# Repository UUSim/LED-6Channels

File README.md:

# 6 Channel LED controller board
This project hosts the Eagle-based design of a 6 channel LED controller.

The device features:
- DC power (rated 7-12V)
- Powered via i2c bus connector (TBD)
- Controlled via 3 rotary encoders:
  - Intensity for 2 separate LED sections
  - One color wheel
- Clock with battery backup
- Programming header
- External i2c-bus connector

The 6 channels are configured as follows:
- 1 RGB connector
- 3 separate connectors for a color of choice

Note: The board is layed out such that diy etching is possible using double-sided UV-lighting and etching. The traces are routed such that the number of vias is kept to a minimum (avoiding trough-hole plating).

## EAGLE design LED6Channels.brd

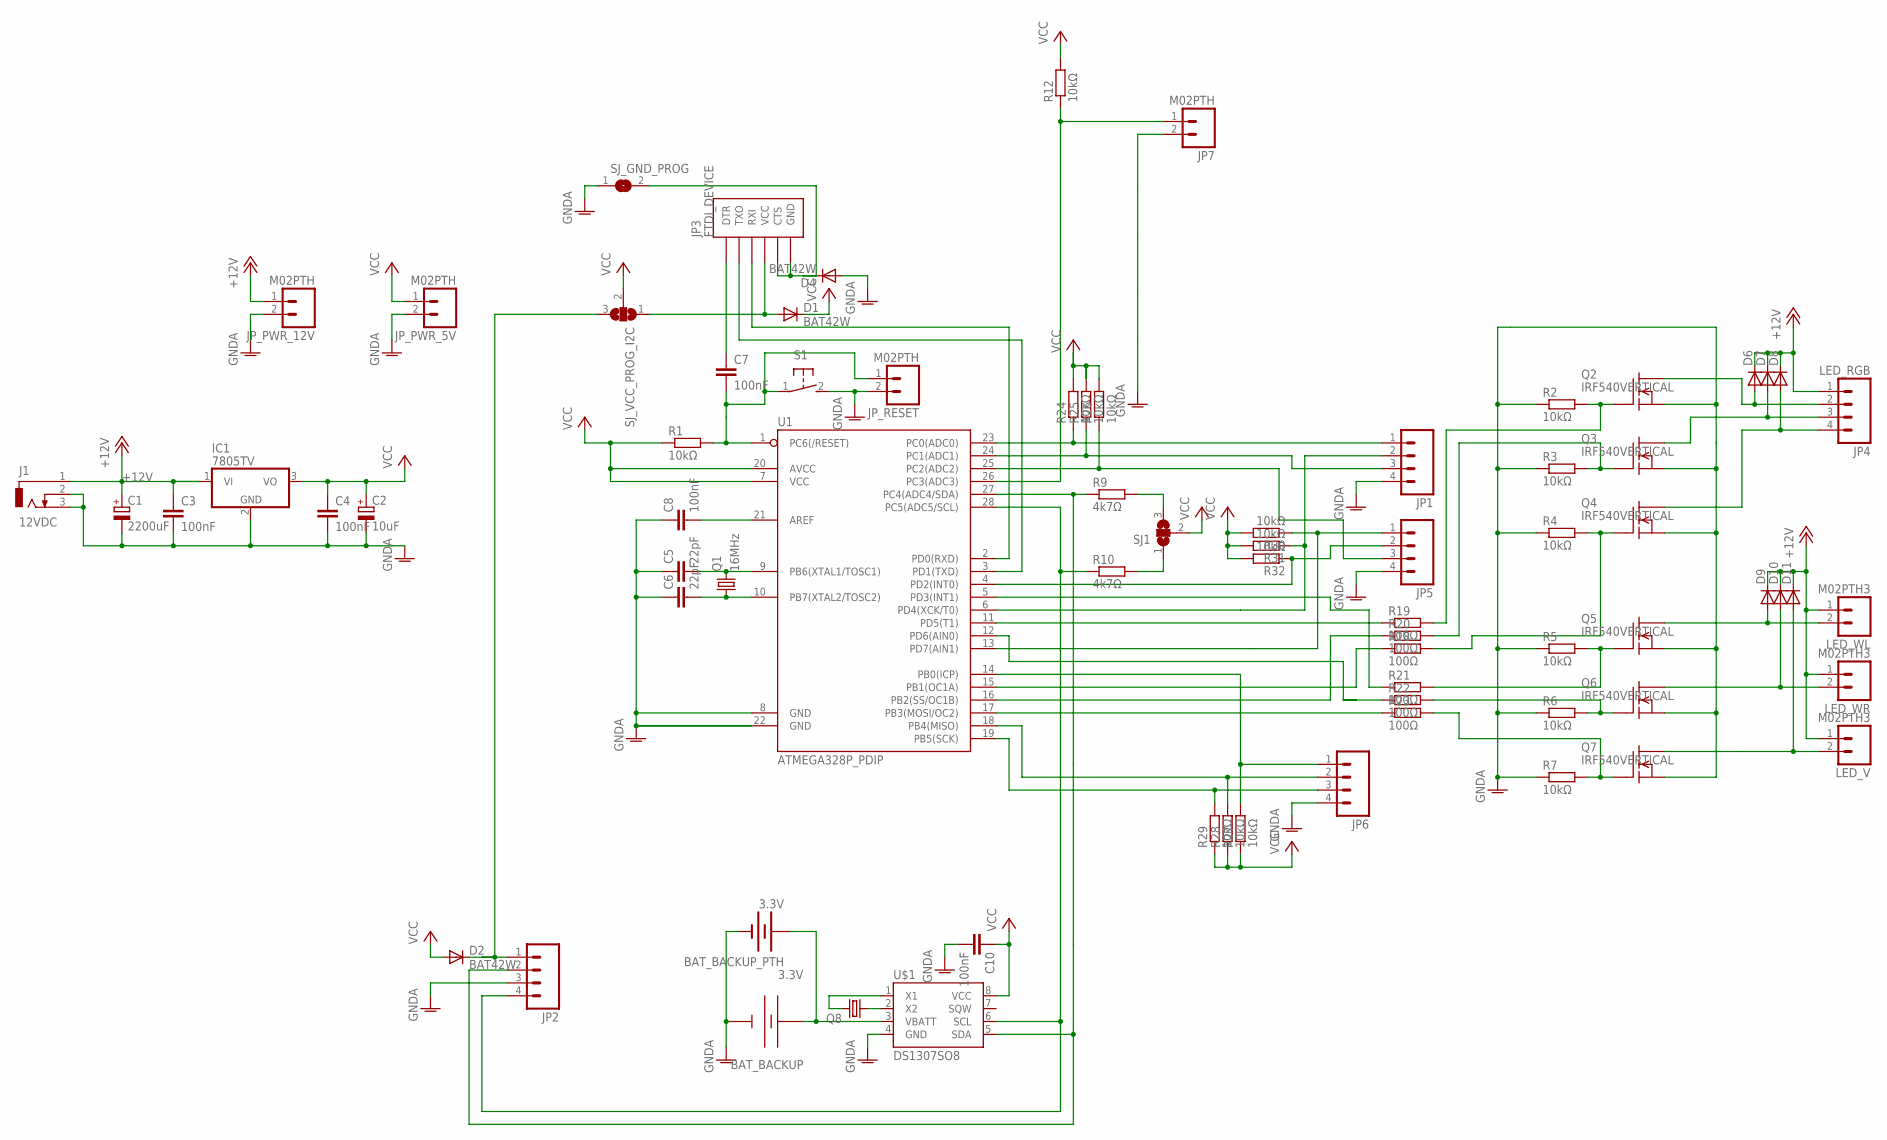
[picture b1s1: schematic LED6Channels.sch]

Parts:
BAT_BACKUP: 3.3V; S8421-45R-NOVIAS
BAT_BACKUP_PTH: 3.3V; BATTCOM_20MM_PTH
C1: 2200uF; E5-13
C2: 10uF; E2-5
C3, C4, C7, C8, C10: 100nF; C025-024X044
C5, C6: 22pF; C025-024X044
D1, D2, D4: BAT42W; SOD123
D6, D7, D8, D9, D10, D11: DIODE-DO201-05V; DO201AD-05V
IC1: 7805TV; TO220V
J1: 12VDC; DCJ0303
JP1, JP2, JP5, JP6: M04LONGPADS; 1X04_LONGPADS
JP3: FTDI_DEVICE; FTDI_DEVICE_SIDE
JP4: LED_RGB; 1X04_LONGPADS
JP7: M02PTH; 1X02
JP_PWR_5V, JP_PWR_12V: M02PTH; 1X02
JP_RESET: M02PTH; 1X02
LED_V: M02PTH3; 1X02_LONGPADS
LED_WL: M02PTH3; 1X02_LONGPADS
LED_WR: M02PTH3; 1X02_LONGPADS
Q1: 16MHz; HC49/S
Q2, Q3, Q4, Q5, Q6, Q7: IRF540VERTICAL; TO220V
Q8: CRYSTALTC26H; TC26H
R1, R2, R3, R4, R5, R6, R7, R12, R24, R25, R26, R27, R28, R29, R30, R31, R32: 10kΩ; 0207/10
R9, R10: 4k7Ω; 0207/10
R18, R19, R20, R21, R22, R23: 100Ω; 0207/10
S1: 31-XX; B3F-31XX
SJ1: SJ2W; SJ_2
SJ_GND_PROG: SJ
SJ_VCC_PROG_I2C: SJ2W; SJ_2
U1: ATMEGA328P_PDIP; DIL28-3
U$1: DS1307SO8; SO08

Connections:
+12V: C1.+, C3.1, D6.C, D7.C, D8.C, D9.C, D10.C, D11.C, IC1.1 (VI), J1.1, JP4.1, JP_PWR_12V.1, LED_V.1, LED_WL.1, LED_WR.1
E1_BUTTON: JP1.3, R25.1, U1.24 (PC1(ADC1))
E1_L: JP1.1, R24.1, U1.23 (PC0(ADC0))
E1_R: JP5.3, R26.1, U1.25 (PC2(ADC2))
E2_BUTTON: JP1.2, R31.1, U1.6 (PD4(XCK/T0))
E2_L: JP5.2, R32.1, U1.4 (PD2(INT0))
E2_R: JP5.1, R30.1, U1.13 (PD7(AIN1))
GNDA: BAT_BACKUP.2 (-), BAT_BACKUP_PTH.2 (-), C1.-, C2.-, C3.2, C4.2, C5.1, C6.1, C8.1, C10.2, D4.A, IC1.2 (GND), J1.2, J1.3, JP1.4, JP2.3, JP5.4, JP6.4, JP7.2, JP_PWR_5V.2, JP_PWR_12V.2, JP_RESET.2, Q2.3 (S), Q3.3 (S), Q4.3 (S), Q5.3 (S), Q6.3 (S), Q7.3 (S), R2.1, R3.1, R4.1, R5.1, R6.1, R7.1, S1.2 (S), SJ_GND_PROG.1, U1.8 (GND), U1.22 (GND), U$1.4 (GND)
unnamed: Q7.1 (G), R7.2, R23.2
unnamed: R23.1, U1.17 (PB3(MOSI/OC2))
unnamed: Q6.1 (G), R6.2, R22.2
unnamed: R20.1, U1.16 (PB2(SS/OC1B))
unnamed: R18.1, U1.15 (PB1(OC1A))
unnamed: R21.1, U1.5 (PD3(INT1))
unnamed: Q3.1 (G), R3.2, R20.2
unnamed: Q2.1 (G), R2.2, R19.2
unnamed: D10.A, LED_WR.2, Q6.2 (D)
unnamed: D9.A, LED_WL.2, Q5.2 (D)
unnamed: D11.A, LED_V.2, Q7.2 (D)
unnamed: D6.A, JP4.2, Q2.2 (D)
unnamed: D7.A, JP4.3, Q3.2 (D)
unnamed: C8.2, U1.21 (AREF)
unnamed: JP6.2, R28.2, U1.18 (PB4(MISO))
unnamed: JP6.3, R29.2, U1.19 (PB5(SCK))
unnamed: JP6.1, R27.2, U1.14 (PB0(ICP))
unnamed: Q5.1 (G), R5.2, R21.2
unnamed: R19.1, U1.11 (PD5(T1))
unnamed: R22.1, U1.12 (PD6(AIN0))
unnamed: Q4.1 (G), R4.2, R18.2
unnamed: D8.A, JP4.4, Q4.2 (D)
OSC1: C5.2, Q1.2, U1.9 (PB6(XTAL1/TOSC1))
OSC2: C6.2, Q1.1, U1.10 (PB7(XTAL2/TOSC2))
PIN_EXTRA: JP7.1, R12.1, U1.26 (PC3(ADC3))
P_GND: D4.C, JP3.P$5 (CTS), JP3.P$6 (GND), SJ_GND_PROG.2
P_RESET: C7.1, JP3.P$1 (DTR)
P_RX: JP3.P$3 (RXI), U1.2 (PD0(RXD))
P_TX: JP3.P$2 (TXO), U1.3 (PD1(TXD))
P_VCC: D1.A, JP3.P$4 (VCC), SJ_VCC_PROG_I2C.1
RESET: C7.2, JP_RESET.1, R1.2, S1.1, U1.1 (PC6(/RESET))
SCL: JP2.4, R10.1, U1.28 (PC5(ADC5/SCL)), U$1.6 (SCL)
SCL_PULLUP_JUMP: R10.2, SJ1.1
SDA: JP2.2, R9.1, U1.27 (PC4(ADC4/SDA)), U$1.5 (SDA)
SDA_PULLUP_JUMP: R9.2, SJ1.3
VBAT: BAT_BACKUP.1 (+), BAT_BACKUP_PTH.1 (+), U$1.3 (VBATT)
VCC: C2.+, C4.1, C10.1, D1.C, D2.A, IC1.3 (VO), JP_PWR_5V.1, R1.1, R12.2, R24.2, R25.2, R26.2, R27.1, R28.1, R29.1, R30.2, R31.2, R32.2, SJ1.2, SJ_VCC_PROG_I2C.2, U1.7 (VCC), U1.20 (AVCC), U$1.8 (VCC)
VCC_I2C: D2.C, JP2.1, SJ_VCC_PROG_I2C.3
X1: Q8.2, U$1.1 (X1)
X2: Q8.1, U$1.2 (X2)

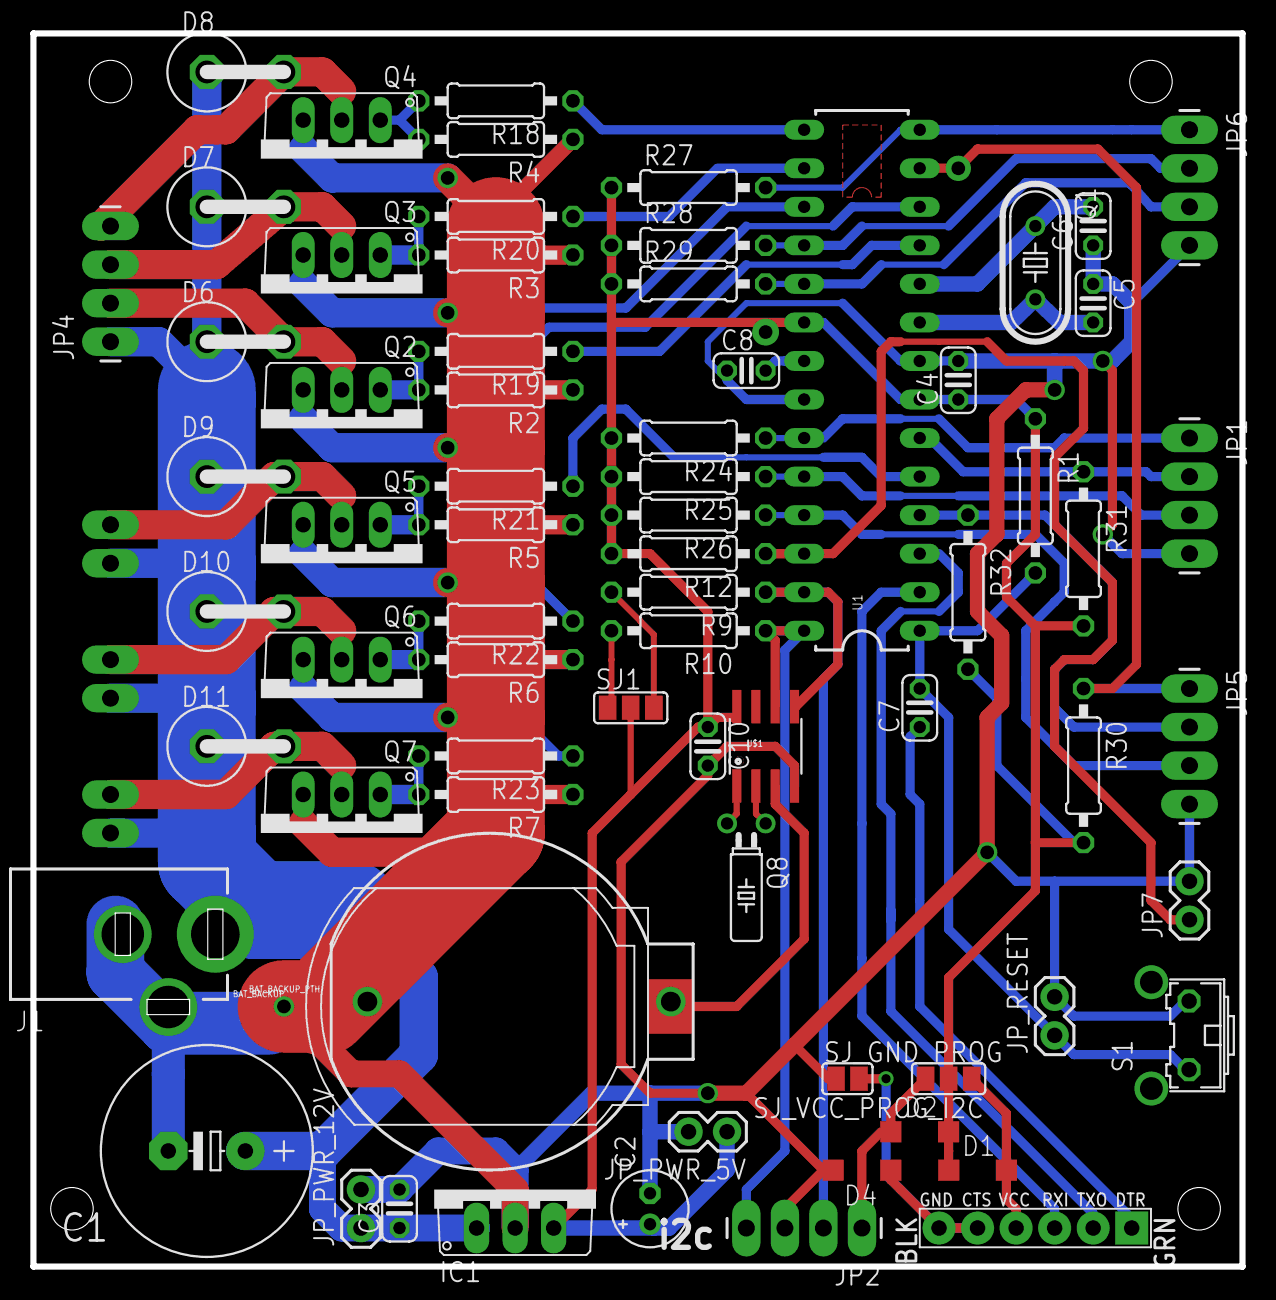
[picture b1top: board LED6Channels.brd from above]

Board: 2 copper layers, 79.7 x 81.3 mm, 74 parts (0 on the bottom side), 48 nets.

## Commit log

2017-01-16 Added screenshot of board layout
2017-01-16 Added project description
2017-01-25 Added Eagle design files
    Added schematic and board files

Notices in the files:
parts and their libraries:
SparkFun-DigitalIC: Licensing: CC v3.0 Share-Alike You are welcome to use this library for commercial purposes.
SparkFun-FreqCtrl: Licensing: Creative Commons ShareAlike 4.0 International - https://creativecommons.org/licenses/by-sa/4.0
